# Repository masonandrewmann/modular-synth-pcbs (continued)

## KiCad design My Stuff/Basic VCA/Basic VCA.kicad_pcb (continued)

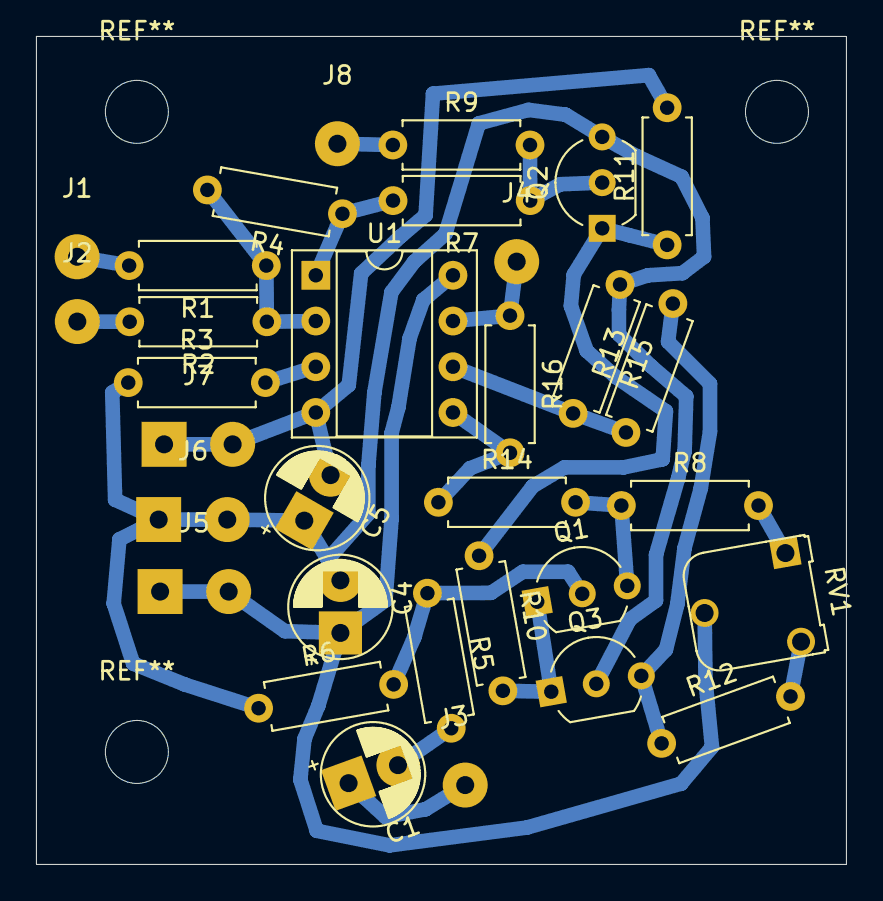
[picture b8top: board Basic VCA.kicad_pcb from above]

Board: 2 copper layers, 45.0 x 46.0 mm, 32 parts (0 on the bottom side), 22 nets.

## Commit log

2020-12-14 hiiii
2020-12-14 wow pcbs
2021-01-03 whoops
2021-01-03 added component list and datasheets uwu
2021-01-03 datasheets for 2N3906 and 2N3904 added
2021-01-03 replaced bad datasheets
2021-01-04 more sheetzp-0o
2021-01-04 finished schematic, placed and arranged parts on pcbnew
2021-01-04 fixed some incorrect component values
2021-01-04 pcb design for VCA finished
2021-01-05 fixed a schematic error with transistor pinout. pcb not updated yet
2021-01-05 fixed transistor pinout on pcb
2021-01-05 added ground fills and vias to shorten ground paths
2021-01-05 fixed a bad via and exported gerber and drl files
2021-01-05 silkscreen cleanup
2021-01-05 cleaned up pcb, fixed bridge rectifier pinout, added silkscreen and exported fabrication files
2021-01-05 added BOM file
2021-01-07 added design rule screenshots
2021-01-11 checked over schematic and added footprints for all but capacitors
2021-01-11 assigned footprints
2021-01-11 layout passes drc
2021-01-11 silkscreen designators placed
2021-01-11 doodled on silkscreen
2021-01-13 checked schematic and assigned footprints
2021-01-13 placed components in general location on pcb uwu
2021-01-17 VCF PCB
2021-01-17 hi i miight have done smth i dont remember uwu
2021-01-24 idk maybe i changed smth
2021-01-24 added functional silkscreen
2021-01-24 fixed error on silkscreen (input/output labels)
2021-01-24 made silkscreen pretty
2021-01-25 vcf done
2021-01-25 hiiiii
2021-01-29 added schematic for VC reverb
2021-01-30 placed components on pcb, some caps i think have the wrong footprint
2021-01-30 progress on wiring
2021-02-01 finished back copper connections
2021-03-07 probably changed some stuff idk
2021-04-04 added serge USG
2021-04-04 added power connectors to DUSG
2021-04-04 DUSG fabrication outputs added
2021-04-05 DUSG updates
2021-04-12 datasheets and BOM
2021-05-08 lots of stuff tbh
2021-05-08 fixed error and rerouted VCO
2021-05-09 finished sequencer schematic
2021-05-09 checked over sequencer schematic
2021-05-09 VCO - added tempco resistor holes
2021-05-09 added totem pole VCF
2021-05-09 fixed eagle gerbers
2021-05-12 sequencer pcb designed and base silkscreen
2021-05-12 hiii
2021-05-12 added micro sample hold schematic
2021-05-12 triple waveshaper schematic added
2021-05-12 added noise cornu schematic
2021-05-12 added triple waveshaper pcb
2021-05-12 sample hold pcb added
2021-05-12 pwr connector silkscreen
2021-05-12 added noise pcb
2021-05-13 made silkscreens pretty
2021-05-13 beep
2021-05-18 front panel work
2021-05-19 Finished ambisonics schematics
2021-05-19 moved samplehold file
2021-05-20 ambisonic pcbsdoneee
2021-05-21 finished/plotted ambisonic PCBs
2021-05-26 added more panel desiigns
2021-05-30 added some new boards
2021-05-30 cleaned up silkscreen
2021-05-30 ssg work
2021-05-30 cleaned up ssg silkscreen
2021-05-30 cleaned up voltage quantizer silkscreen
2021-07-18 literally so much stuff
2021-09-21 ooh some new pcbs yayy
2021-09-21 testing token
